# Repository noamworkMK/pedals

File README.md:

Pitch Shifter:

System Overview
A frequency-tracking pitch shifter  The design avoids digital DSP in favor of a CD4046 Phase-Locked Loop (PLL) and CD4017 decade counter 
for interval sequencing.

im very connected to music and rock culture, and its all started when i talked with my friend about how expansive effect pedal are. and then i thought, maybe i can build one, so from there i searched for like a month on how to buld them, about the electronics of the audio, and the logic. and i asked myself how can i make it. and then i found kicad as almost the only free softwere that worked for me, and i learned how to use it, this project has alot of versions some of them are really bad, but thats how i learned to design a pcb.

the pcb design: 
this pcb design had a lot of changes, at first i had a 2 layers board, unorgenised and to big to be in the enclouser, and then i made it smaller, changed some foorpeint, rerouthed the pcb, added fillings, and i almost sent it for prodaction like that. and then i felt that something is misssing, and that i wanted to create a intresting pedal that will be good and easy, so in this version i addad relay switch to create a bypass and added caps and, more diods, and resistors to protect the parts from overload, backcurent, and stuff that willl ruin the board. and i changed the board size and redone the traces again to finaly fit my expactation and the enclouser. 

the leyers of the pcb: 

the circuit: 
The circuit takes an audio, signal shifts its pitch down and outputs it with 5 selectable pitch steps controlled by a push button. The core chips are a CD4046 (handles the pitch shifting) and a CD4017 counter (steps through the 5 settings). A TL072 op-amp buffers the input signal, and five NSL-32 optocouplers that i swiched to VTL5C4 in prodaction becouse of avilablity. this optocouplers (optical) do the switching between pitch steps without noise, becouse there is not current passing between them.

logic schematics:

audio schematics:

the battery compartment: 
i sd designed a 9v battary compartment in solidworks that will fit exactly in the enclouser

assembly:
i also created a 3d assambly of the pedal in solidworks, the assembly is partial becouse it would take me a lot of time to do every thing and its mainly for fitting and concepts. but the main parts are in there.

Technical Specifications:

Frequency Synthesis: CD4046 PLL tracks input frequency; CD4017 logic handles interval division/multiplication.
Analog Interface: VTL5C4 Vactrols integrated for smooth interval transitions.
Calibration: 5x 50k  trimmers for precise frequency offset tuning.
Input Stage: TL072 op-amp buffer for high-impedance guitar signal integrity.
Bypass: Relay-based switching system for transparent operation.

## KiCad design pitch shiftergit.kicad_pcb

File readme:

Pitch Shifter:

System Overview
A frequency-tracking pitch shifter utilizing a CMOS-based architecture. The design avoids digital DSP in favor of a CD4046 Phase-Locked Loop (PLL) and CD4017 decade counter 
for interval sequencing.

Technical Specifications:

Frequency Synthesis: CD4046 PLL tracks input frequency; CD4017 logic handles interval division/multiplication.
Analog Interface: NSL-32 Vactrols integrated for smooth interval transitions.
Calibration: 5x 50k on-board trimmers for precise frequency offset tuning.
Input Stage: TL072 op-amp buffer for high-impedance guitar signal integrity.
Bypass: Relay-based switching system for transparent operation.

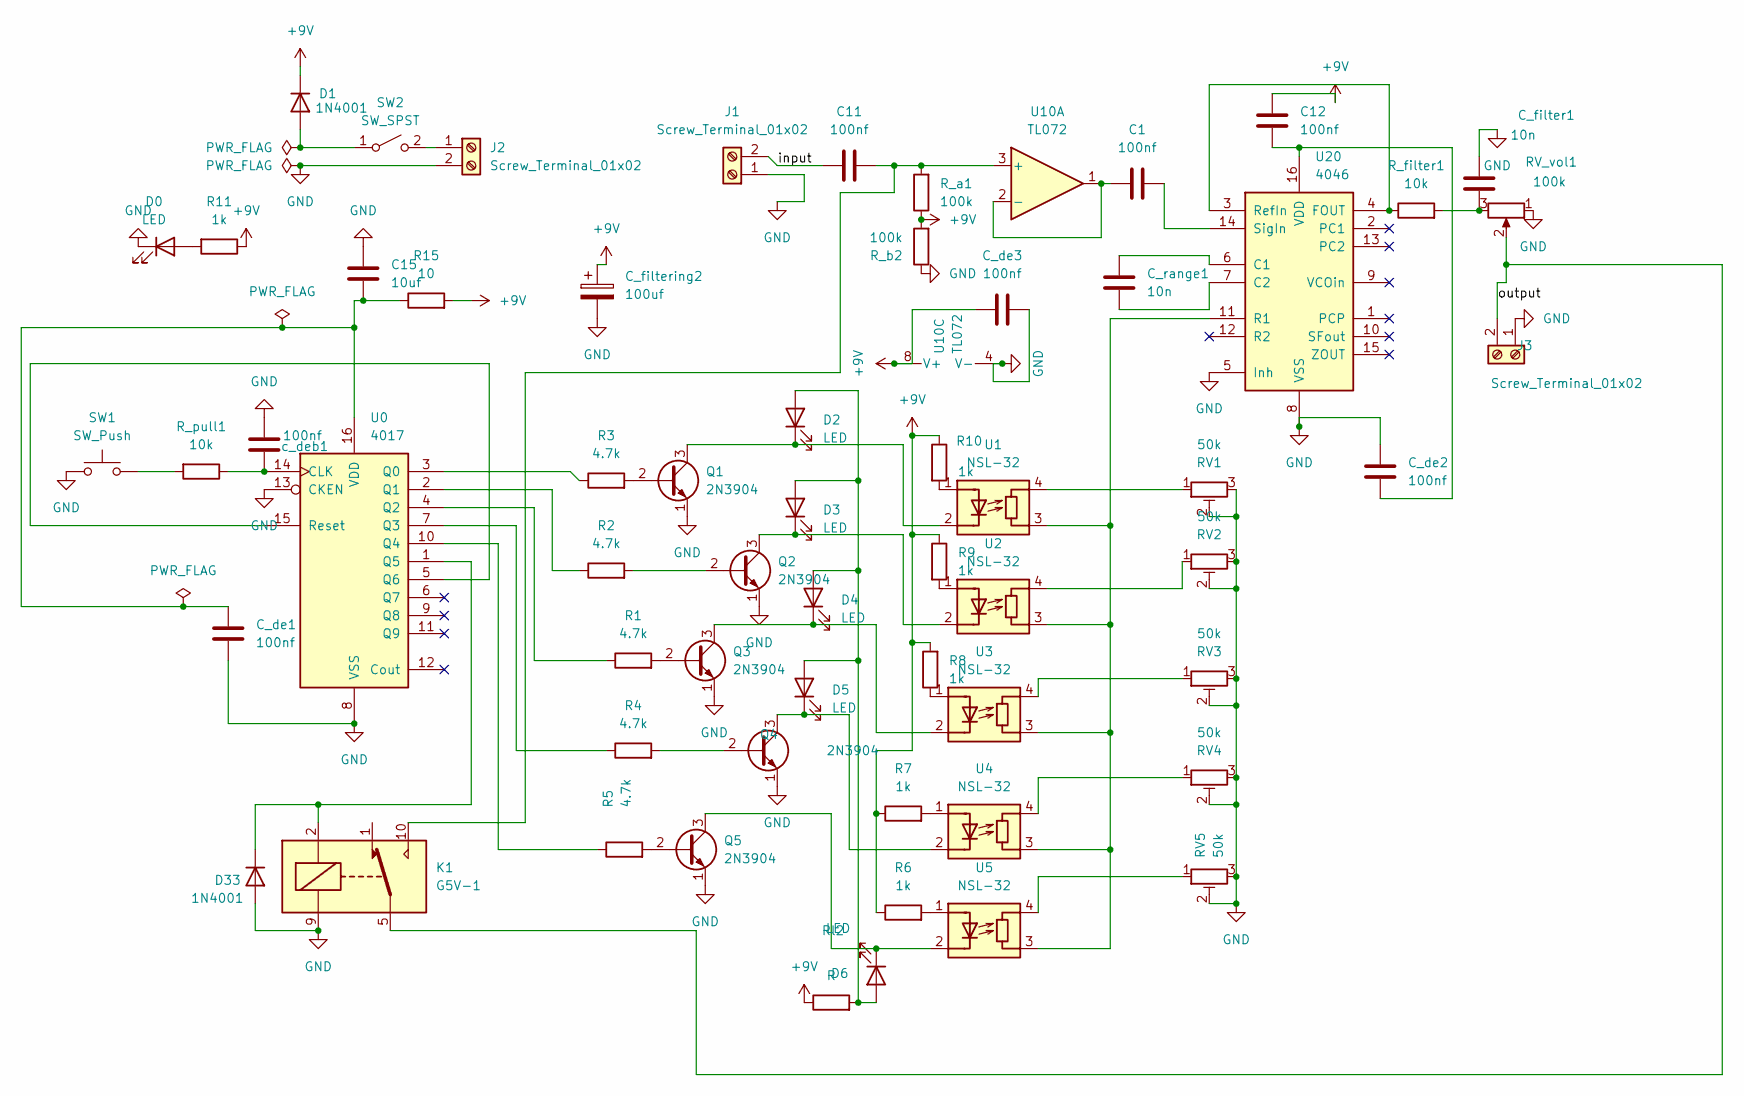
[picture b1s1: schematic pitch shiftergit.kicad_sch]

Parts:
C1, C11, C12: 100nf; C_Disc_D5.0mm_W2.5mm_P2.50mm
C15: 10uf; CP_Radial_D5.0mm_P2.50mm
C_de1, C_de2, C_de3: 100nf; C_Disc_D5.0mm_W2.5mm_P5.00mm
C_filter1: 10n; C_Disc_D5.0mm_W2.5mm_P2.50mm
C_filtering2: 100uf; CP_Radial_D5.0mm_P2.00mm
C_range1: 10n; C_Disc_D5.0mm_W2.5mm_P2.50mm
D0, D2, D3, D4, D5, D6: LED; SolderWire-0.75sqmm_1x02_P4.8mm_D1.25mm_OD2.3mm
D1, D33: 1N4001; D_DO-41_SOD81_P10.16mm_Horizontal
J1, J2, J3: Screw_Terminal_01x02; SolderWire-0.75sqmm_1x02_P4.8mm_D1.25mm_OD2.3mm
K1: G5V-1; Relay_SPDT_Omron_G5V-1
Q1, Q2, Q3, Q4, Q5: 2N3904; TO-92_Inline
R1, R2, R3, R4, R5: 4.7k; R_Axial_DIN0207_L6.3mm_D2.5mm_P7.62mm_Horizontal
R6, R7, R8, R9, R10, R11: 1k; R_Axial_DIN0207_L6.3mm_D2.5mm_P7.62mm_Horizontal
R15: 10; R_Axial_DIN0207_L6.3mm_D2.5mm_P7.62mm_Horizontal
RV1, RV2, RV3, RV4, RV5: 50k; Potentiometer_Bourns_3296W_Vertical
RV_vol1: 100k; SolderWire-0.75sqmm_1x03_P4.8mm_D1.25mm_OD2.3mm
R_a1: 100k; R_Axial_DIN0207_L6.3mm_D2.5mm_P7.62mm_Horizontal
R_b2: 100k; R_Axial_DIN0207_L6.3mm_D2.5mm_P7.62mm_Horizontal
R_filter1: 10k; R_Axial_DIN0207_L6.3mm_D2.5mm_P7.62mm_Horizontal
R_pull1: 10k; R_Axial_DIN0207_L6.3mm_D2.5mm_P7.62mm_Horizontal
Rl2: R; R_Axial_DIN0207_L6.3mm_D2.5mm_P7.62mm_Horizontal
SW1: SW_Push; SolderWire-0.75sqmm_1x02_P4.8mm_D1.25mm_OD2.3mm
SW2: SW_SPST; SolderWire-0.75sqmm_1x02_P4.8mm_D1.25mm_OD2.3mm
U0: 4017; DIP-16_W7.62mm
U1, U2, U3, U4, U5: NSL-32; Luna_NSL-32
U10: TL072; DIP-8_W7.62mm
U20: 4046; DIP-16_W7.62mm
c_deb1: 100nf; C_Disc_D5.0mm_W2.5mm_P2.50mm

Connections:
+9V: C12.1, C_de3.1, C_filtering2.1, D1.1 (K), R6.1, R7.1, R8.2, R9.1, R10.1, R11.1, R15.2, R_a1.1, R_b2.2, Rl2.1, U10.8 (V+)
/input: C11.1, J1.2
/output: J3.2, K1.5, K1.6, RV_vol1.2
GND: C15.1, C_de1.2, C_de2.1, C_de3.2, C_filter1.1, C_filtering2.2, D0.1 (K), D33.2 (A), J1.1, J2.2, J3.1, K1.9, Q1.1 (E), Q2.1 (E), Q3.1 (E), Q4.1 (E), Q5.1 (E), RV1.2, RV1.3, RV2.2, RV2.3, RV3.2, RV3.3, RV4.2, RV4.3, RV5.2, RV5.3, RV_vol1.1, R_b2.1, SW1.1, U0.8 (VSS), U0.13 (CKEN), U10.4 (V-), U20.5 (Inh), U20.8 (VSS), c_deb1.1
unnamed: C_filter1.2, RV_vol1.3, R_filter1.2
unnamed: D0.2 (A), R11.2
unnamed: D1.2 (A), SW2.1 (A)
unnamed: D2.2 (A), D3.2 (A), D4.2 (A), D5.2 (A), D6.2 (A), Rl2.2
unnamed: D2.1 (K), Q1.3 (C), U1.2 (K)
unnamed: D3.1 (K), Q2.3 (C), U2.2 (K)
unnamed: D4.1 (K), Q3.3 (C), U3.2 (K)
unnamed: D5.1 (K), Q4.3 (C), U4.2 (K)
unnamed: D6.1 (K), Q5.3 (C), U5.2 (K)
unnamed: D33.1 (K), K1.2, U0.1 (Q5)
unnamed: J2.1, SW2.2 (B)
unnamed: Q1.2 (B), R3.2
unnamed: Q2.2 (B), R2.2
unnamed: Q3.2 (B), R1.2
unnamed: Q4.2 (B), R4.2
unnamed: Q5.2 (B), R5.2
unnamed: RV1.1, U1.4 (R)
unnamed: RV2.1, U2.4 (R)
unnamed: RV3.1, U3.4 (R)
unnamed: RV4.1, U4.4 (R)
unnamed: RV5.1, U5.4 (R)
unnamed: R_pull1.2, SW1.2
unnamed: R_pull1.1, U0.14 (CLK), c_deb1.2
unnamed: R3.1, U0.3 (Q0)
unnamed: R2.1, U0.2 (Q1)
unnamed: R1.1, U0.4 (Q2)
unnamed: R4.1, U0.7 (Q3)
unnamed: R5.1, U0.10 (Q4)
unnamed: U0.5 (Q6), U0.15 (Reset)
unnamed: C15.2, C_de1.1, R15.1, U0.16 (VDD)
unnamed: R10.2, U1.1 (A)
unnamed: R9.2, U2.1 (A)
unnamed: R8.1, U3.1 (A)
unnamed: R7.2, U4.1 (A)
unnamed: R6.2, U5.1 (A)
unnamed: C11.2, K1.10, R_a1.2, U10.3 (+)
unnamed: C1.1, U10.1, U10.2 (-)
unnamed: C_range1.1, U20.6 (C1)
unnamed: C_range1.2, U20.7 (C2)
unnamed: R_filter1.1, U20.3 (RefIn), U20.4 (FOUT)
unnamed: U1.3 (R), U2.3 (R), U3.3 (R), U4.3 (R), U5.3 (R), U20.11 (R1)
unnamed: C1.2, U20.14 (SigIn)
unnamed: C12.2, C_de2.2, U20.16 (VDD)

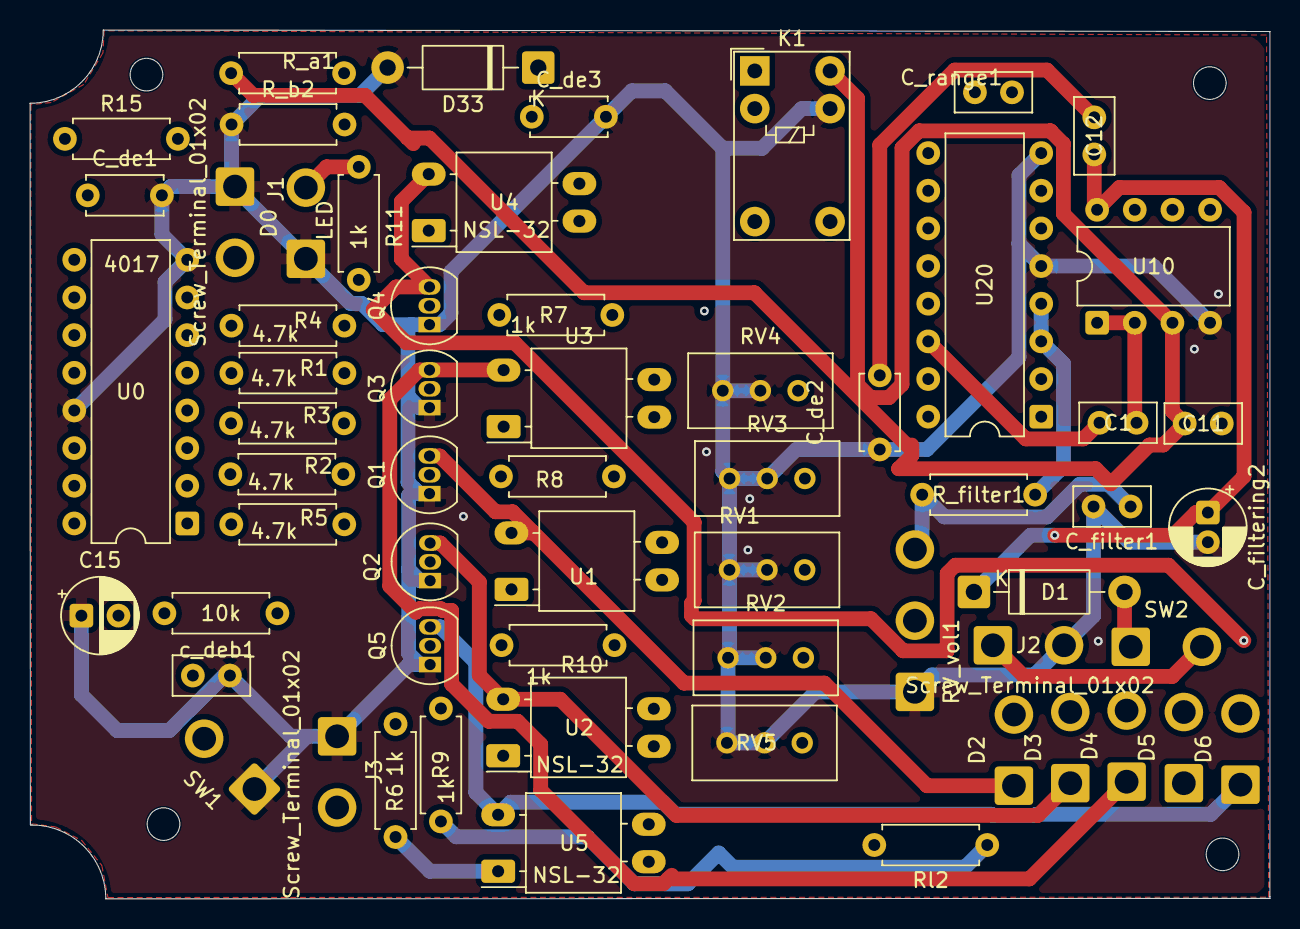
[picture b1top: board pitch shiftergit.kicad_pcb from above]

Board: 4 copper layers, 83.6 x 58.6 mm, 61 parts (0 on the bottom side), 47 nets.

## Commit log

2026-05-14 Add project overview and technical specifications to README
    Added a detailed overview and specifications for the pitch shifter project.
2026-05-14 Add images to README for visual reference
2026-05-16 Enhance README with project details and images
    Expanded the README with personal background, PCB design evolution, circuit details, and assembly information for the pitch shifter project.
